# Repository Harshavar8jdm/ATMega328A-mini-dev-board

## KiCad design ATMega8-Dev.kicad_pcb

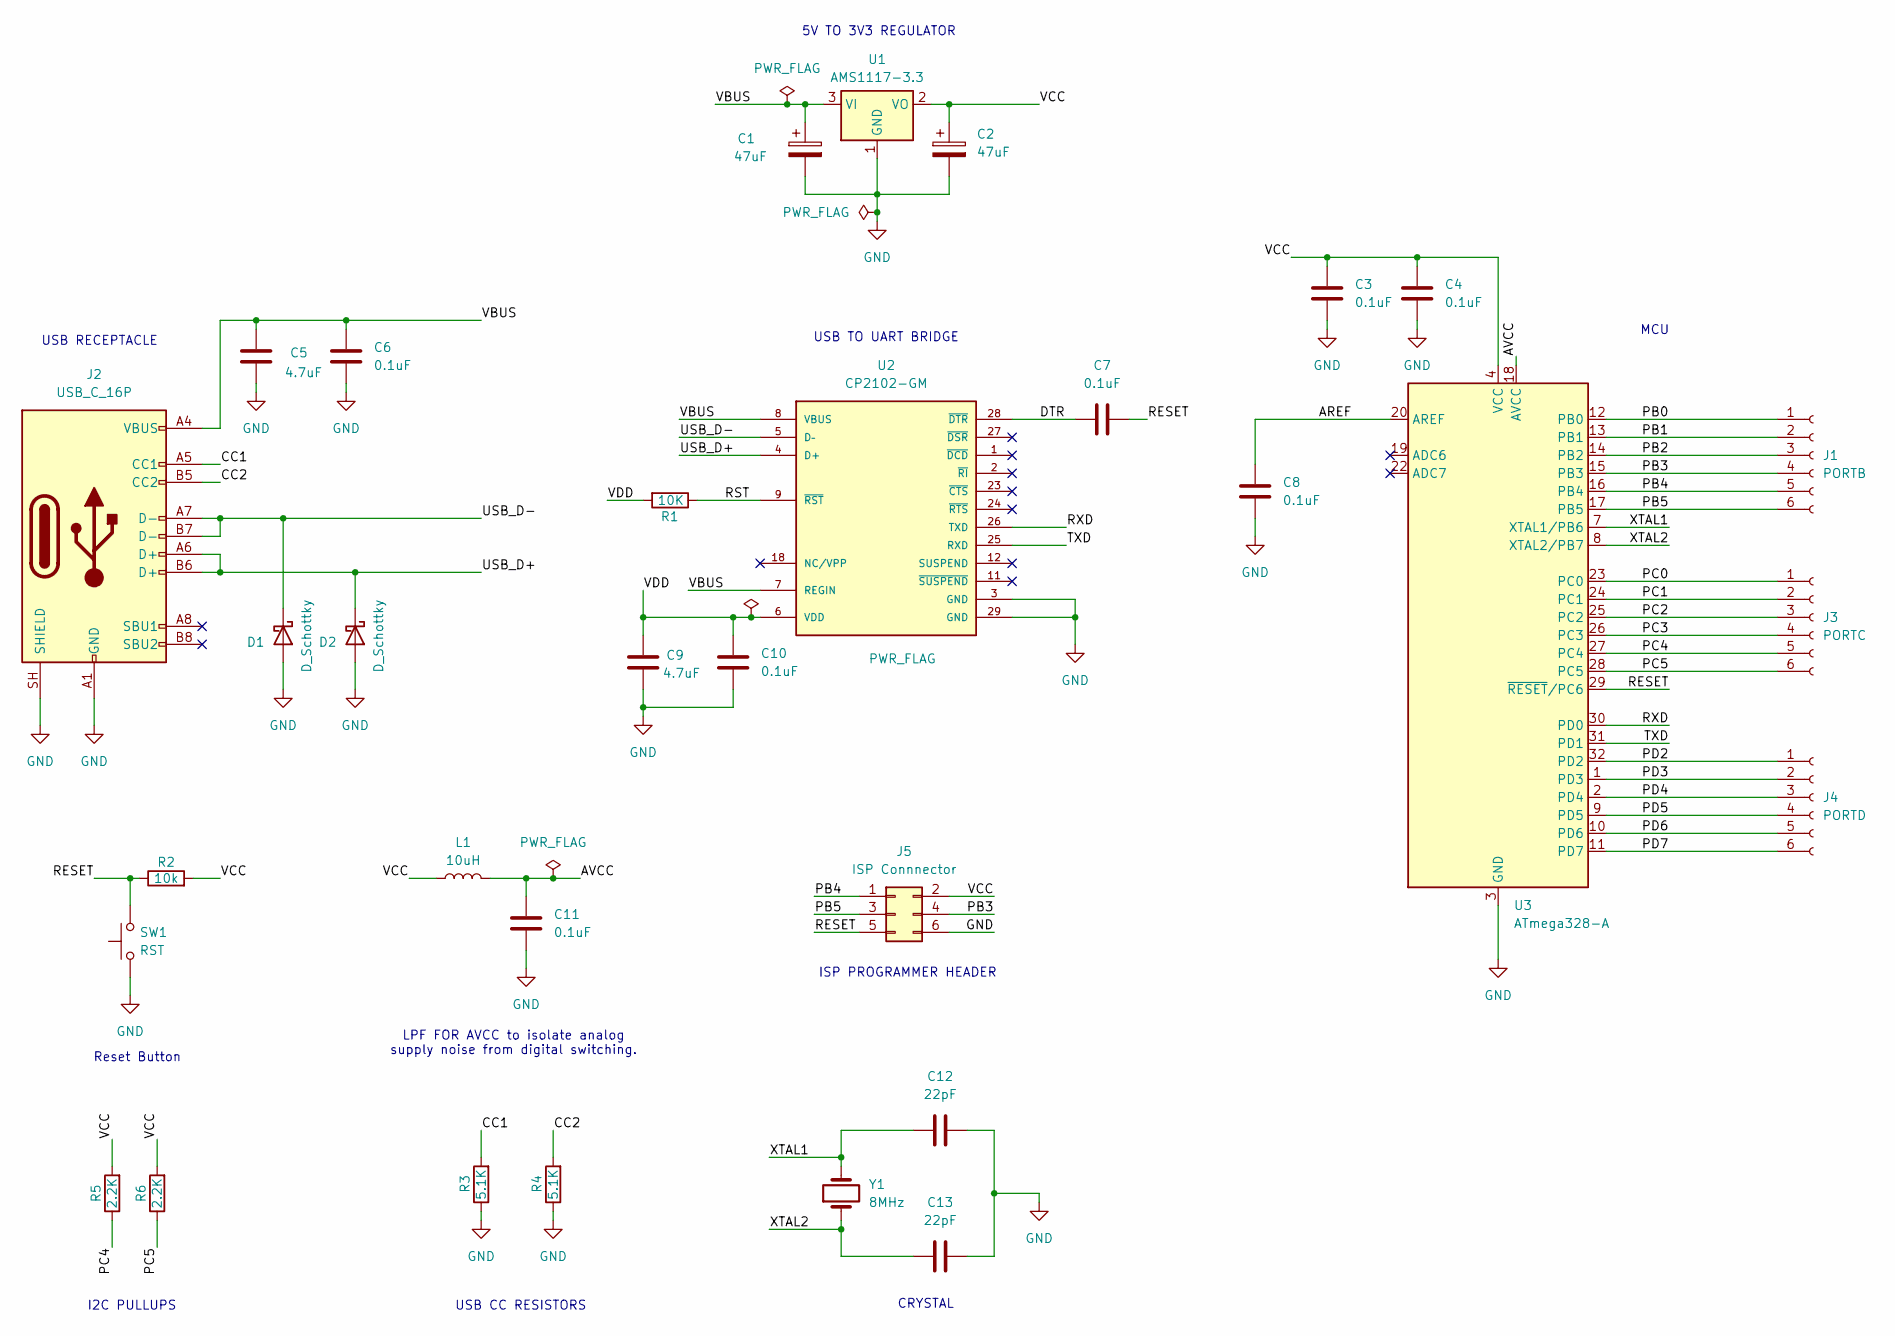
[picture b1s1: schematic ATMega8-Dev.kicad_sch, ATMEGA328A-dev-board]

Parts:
C1, C2: 47uF; C_0805_2012Metric_Pad1.18x1.45mm_HandSolder
C3, C4, C6, C7, C8, C10, C11: 0.1uF; C_0603_1608Metric_Pad1.08x0.95mm_HandSolder
C5, C9: 4.7uF; C_0805_2012Metric_Pad1.18x1.45mm_HandSolder
C12, C13: 22pF; C_0603_1608Metric_Pad1.08x0.95mm_HandSolder
D1, D2: D_Schottky; D_0603_1608Metric_Pad1.05x0.95mm_HandSolder
J1: PORTB; PinSocket_1x06_P2.54mm_Vertical
J2: USB_C_16P; USB_C_Receptacle_HCTL_HC-TYPE-C-16P-01A
J3: PORTC; PinSocket_1x06_P2.54mm_Vertical
J4: PORTD; PinSocket_1x06_P2.54mm_Vertical
J5: ISP Connnector; PinHeader_2x03_P2.54mm_Vertical
L1: 10uH; L_0805_2012Metric_Pad1.05x1.20mm_HandSolder
R1: 10K; R_0603_1608Metric_Pad0.98x0.95mm_HandSolder
R2: 10k; R_0603_1608Metric_Pad0.98x0.95mm_HandSolder
R3, R4: 5.1K; R_0603_1608Metric_Pad0.98x0.95mm_HandSolder
R5, R6: 2.2K; R_0603_1608Metric_Pad0.98x0.95mm_HandSolder
SW1: RST; SW_Push_SPST_NO_Alps_SKRK
U1: AMS1117-3.3; SOT-223-3_TabPin2
U2: CP2102-GM; QFN50P500X500X100-29N; PARTREV 1.8
U3: ATmega328-A; TQFP-32_7x7mm_P0.8mm
Y1: 8MHz; Crystal_SMD_3215-2Pin_3.2x1.5mm

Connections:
/AREF: C8.2, U3.20 (AREF)
/AVCC: C11.2, L1.2, U3.18 (AVCC)
/CC1: J2.A5 (CC1), R3.2
/CC2: J2.B5 (CC2), R4.2
/DTR: C7.2, U2.28 (~DTR)
/PB0: J1.1, U3.12 (PB0)
/PB1: J1.2, U3.13 (PB1)
/PB2: J1.3, U3.14 (PB2)
/PB3: J1.4, J5.4, U3.15 (PB3)
/PB4: J1.5, J5.1, U3.16 (PB4)
/PB5: J1.6, J5.3, U3.17 (PB5)
/PC0: J3.1, U3.23 (PC0)
/PC1: J3.2, U3.24 (PC1)
/PC2: J3.3, U3.25 (PC2)
/PC3: J3.4, U3.26 (PC3)
/PC4: J3.5, R5.1, U3.27 (PC4)
/PC5: J3.6, R6.1, U3.28 (PC5)
/PD2: J4.1, U3.32 (PD2)
/PD3: J4.2, U3.1 (PD3)
/PD4: J4.3, U3.2 (PD4)
/PD5: J4.4, U3.9 (PD5)
/PD6: J4.5, U3.10 (PD6)
/PD7: J4.6, U3.11 (PD7)
/RESET: C7.1, J5.5, R2.1, SW1.2, U3.29 (~RESET/PC6); also elsewhere on the board
/RST: R1.1, U2.9 (~RST)
/RXD: U2.26 (TXD), U3.30 (PD0)
/TXD: U2.25 (RXD), U3.31 (PD1)
/USB_D+: D2.1 (K), J2.A6 (D+), J2.B6 (D+), U2.4 (D+)
/USB_D-: D1.1 (K), J2.A7 (D-), J2.B7 (D-), U2.5 (D–)
/VBUS: C1.1, C5.1, C6.2, J2.A4 (VBUS), J2.A9 (VBUS), J2.B4 (VBUS), J2.B9 (VBUS), U1.3 (VI), U2.7 (REGIN), U2.8 (VBUS)
/VCC: C2.1, C3.2, C4.2, J5.2, L1.1, R2.2, R5.2, R6.2, U1.2 (VO), U3.4 (VCC), U3.6 (VCC)
/VDD: C9.1, C10.2, R1.2, U2.6 (VDD)
/XTAL1: C12.1, U3.7 (XTAL1/PB6), Y1.2
/XTAL2: C13.1, U3.8 (XTAL2/PB7), Y1.1
GND: C1.2, C2.2, C3.1, C4.1, C5.2, C6.1, C8.1, C9.2, C10.1, C11.1, C12.2, C13.2, D1.2 (A), D2.2 (A), J2.A1 (GND), J2.A12 (GND), J2.B1 (GND), J2.B12 (GND), J2.SH (SHIELD), J5.6, R3.1, R4.1, SW1.1, U1.1 (GND), U2.3 (GND), U2.29 (GND), U2.30, U3.3 (GND), U3.5 (GND), U3.21 (GND); also elsewhere on the board

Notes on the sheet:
MCU
I2C PULLUPS
USB TO UART BRIDGE
CRYSTAL
5V TO 3V3 REGULATOR
Reset Button
USB CC RESISTORS
LPF FOR AVCC to isolate analog supply noise from digital switching.
USB RECEPTACLE
ISP PROGRAMMER HEADER

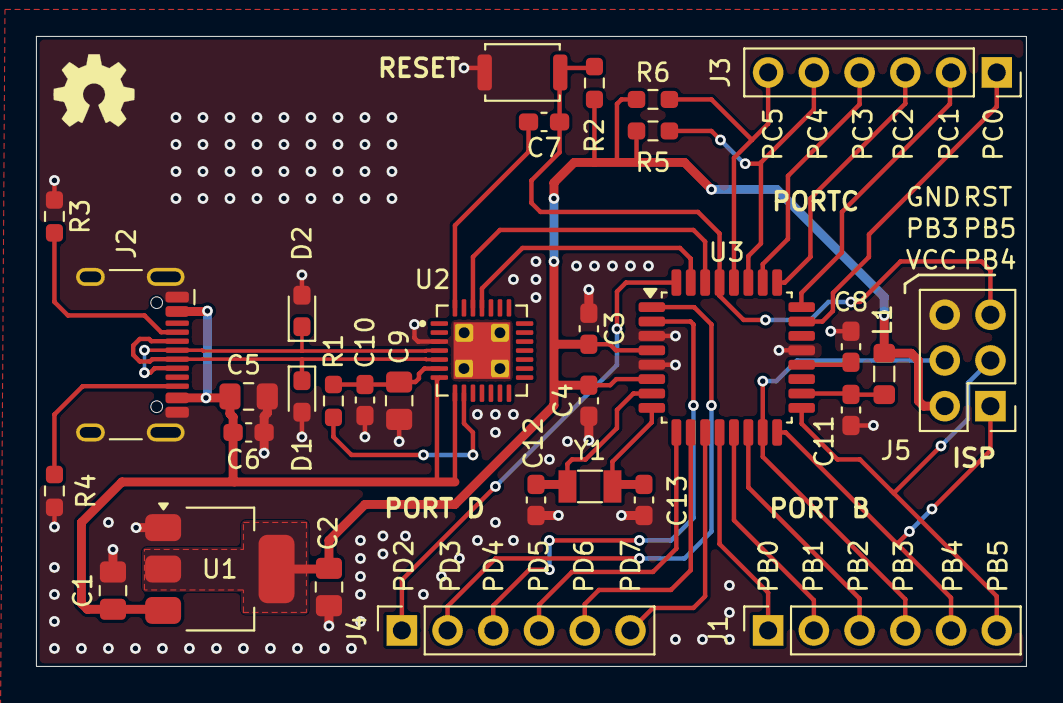
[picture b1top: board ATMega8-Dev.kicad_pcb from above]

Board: 2 copper layers, 55.0 x 35.0 mm, 32 parts (0 on the bottom side), 35 nets.

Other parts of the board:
RESET: RST; SW_Push_SPST_NO_Alps_SKRK

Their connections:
/RESET: RESET.2; also elsewhere on the board
GND: RESET.1; also elsewhere on the board
